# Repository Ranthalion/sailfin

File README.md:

View this project on [CADLAB.io](https://cadlab.io/project/23132). 

"# Sailfin"

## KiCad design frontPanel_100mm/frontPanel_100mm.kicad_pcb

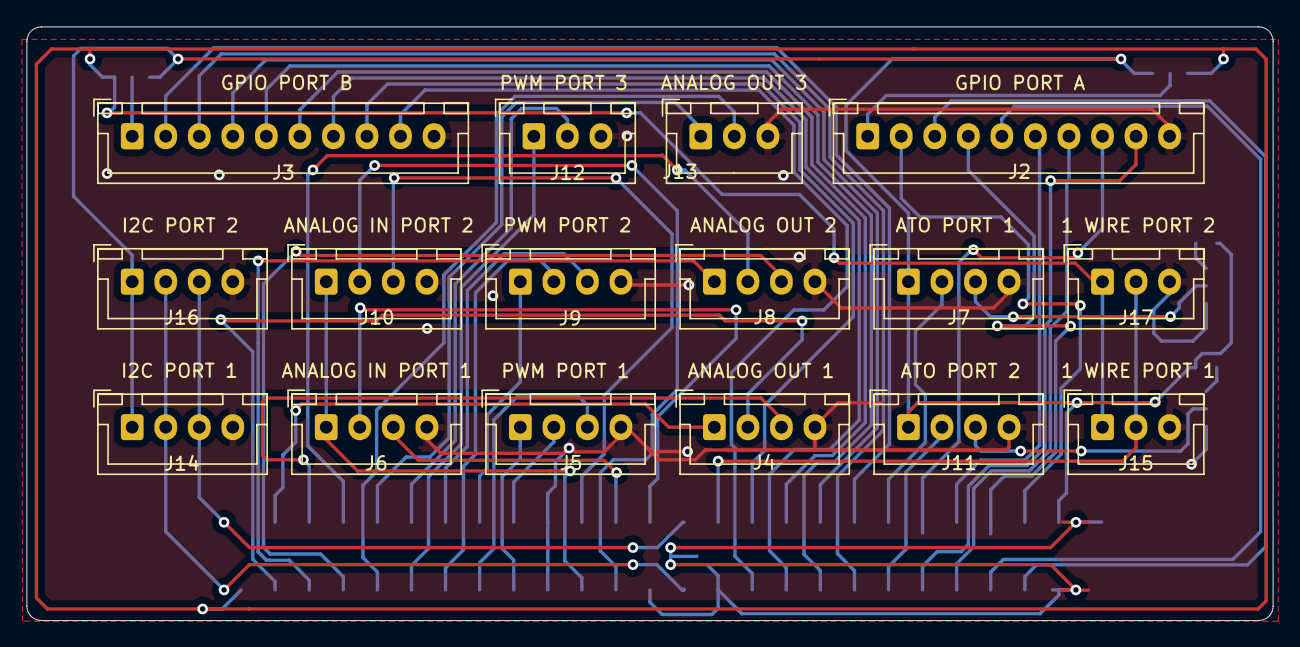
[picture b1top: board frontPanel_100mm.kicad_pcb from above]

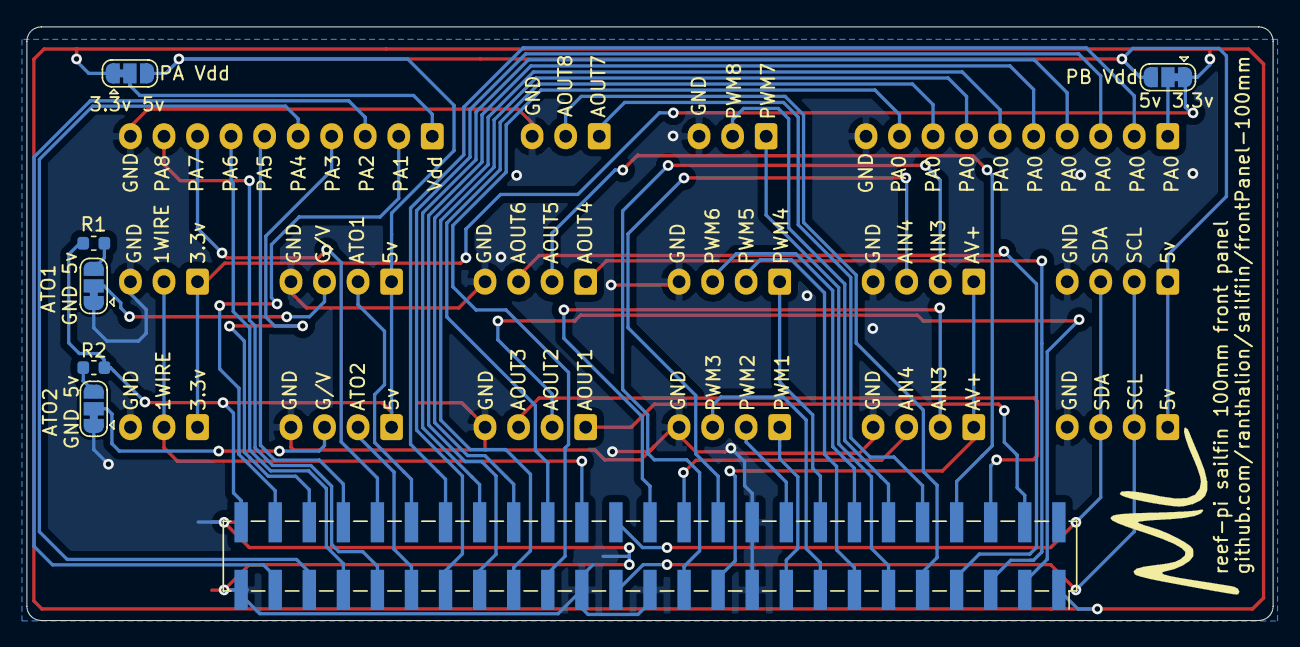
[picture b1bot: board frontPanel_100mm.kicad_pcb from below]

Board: 2 copper layers, 92.9 x 44.3 mm, 23 parts (7 on the bottom side), 51 nets.

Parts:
J1: Conn_02x25_Odd_Even; PinSocket_2x25_P2.54mm_Vertical_SMD
J2: GPIO PORT A; JST_XH_B10B-XH-A_1x10_P2.50mm_Vertical
J3: GPIO PORT B; JST_XH_B10B-XH-A_1x10_P2.50mm_Vertical
J4: ANALOG OUT 1; JST_XH_B04B-XH-A_1x04_P2.50mm_Vertical
J5: PWM PORT 1; JST_XH_B04B-XH-A_1x04_P2.50mm_Vertical
J6: ANALOG IN PORT 1; JST_XH_B04B-XH-A_1x04_P2.50mm_Vertical
J7: ATO PORT 1; JST_XH_B04B-XH-A_1x04_P2.50mm_Vertical
J8: ANALOG OUT 2; JST_XH_B04B-XH-A_1x04_P2.50mm_Vertical
J9: PWM PORT 2; JST_XH_B04B-XH-A_1x04_P2.50mm_Vertical
J10: ANALOG IN PORT 2; JST_XH_B04B-XH-A_1x04_P2.50mm_Vertical
J11: ATO PORT 2; JST_XH_B04B-XH-A_1x04_P2.50mm_Vertical
J12: PWM PORT 3; JST_XH_B03B-XH-A_1x03_P2.50mm_Vertical
J13: ANALOG OUT 3; JST_XH_B03B-XH-A_1x03_P2.50mm_Vertical
J14: I2C PORT 1; JST_XH_B04B-XH-A_1x04_P2.50mm_Vertical
J15: 1 WIRE PORT 1; JST_XH_B03B-XH-A_1x03_P2.50mm_Vertical
J16: I2C PORT 2; JST_XH_B04B-XH-A_1x04_P2.50mm_Vertical
J17: 1 WIRE PORT 2; JST_XH_B03B-XH-A_1x03_P2.50mm_Vertical
JP3: ATO1_Jumper; SolderJumper-3_P1.3mm_Bridged12_RoundedPad1.0x1.5mm
JP4: ATO2_Jumper; SolderJumper-3_P1.3mm_Bridged12_RoundedPad1.0x1.5mm
PA Vdd: PA Voltage; SolderJumper-3_P1.3mm_Bridged12_RoundedPad1.0x1.5mm
PB Vdd: PB Voltage; SolderJumper-3_P1.3mm_Bridged12_RoundedPad1.0x1.5mm
R1: 500; R_0603_1608Metric
R2: R_US; R_0603_1608Metric

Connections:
/1WIRE: J1.30, J15.2, J17.2
/3v3: J1.1, J15.1, J17.1, PA Vdd.1, PB Vdd.1
/5v: J1.50, J7.1, J11.1, J14.1, J16.1, PA Vdd.3, PB Vdd.3, R1.1, R2.1
/AIN1: J1.26, J6.2
/AIN2: J1.24, J6.3
/AIN3: J1.23, J10.2
/AIN4: J1.22, J10.3
/AOUT1: J1.4, J4.1
/AOUT2: J1.3, J4.2
/AOUT3: J1.6, J4.3
/AOUT4: J1.5, J8.1
/AOUT5: J1.8, J8.2
/AOUT6: J1.7, J8.3
/AOUT7: J1.10, J13.1
/AOUT8: J1.9, J13.2
/ATO1: J1.40, J7.2
/ATO2: J1.39, J11.2
/AV+: J1.21, J6.1, J10.1
/PA1: J1.48, J2.2
/PA2: J1.47, J2.3
/PA3: J1.46, J2.4
/PA4: J1.45, J2.5
/PA5: J1.44, J2.6
/PA6: J1.43, J2.7
/PA7: J1.42, J2.8
/PA8: J1.41, J2.9
/PB1: J1.38, J3.2
/PB2: J1.37, J3.3
/PB3: J1.36, J3.4
/PB4: J1.35, J3.5
/PB5: J1.34, J3.6
/PB6: J1.33, J3.7
/PB7: J1.32, J3.8
/PB8: J1.31, J3.9
/PWM1: J1.17, J5.1
/PWM2: J1.18, J5.2
/PWM3: J1.15, J5.3
/PWM4: J1.16, J9.1
/PWM5: J1.13, J9.2
/PWM6: J1.14, J9.3
/PWM7: J1.11, J12.1
/PWM8: J1.12, J12.2
/SCL: J1.27, J14.2, J16.2
/SDA: J1.28, J14.3, J16.3
GND: J1.19, J1.20, J1.25, J1.29, J1.49, J2.10, J3.10, J4.4, J5.4, J6.4, J7.4, J8.4, J9.4, J10.4, J11.4, J12.3, J13.3, J14.4, J15.3, J16.4, J17.3, JP3.1, JP4.1
unnamed: J2.1, PA Vdd.2
unnamed: J3.1, PB Vdd.2
unnamed: J7.3, JP3.2
unnamed: J11.3, JP4.2
unnamed: JP3.3, R1.2
unnamed: JP4.3, R2.2

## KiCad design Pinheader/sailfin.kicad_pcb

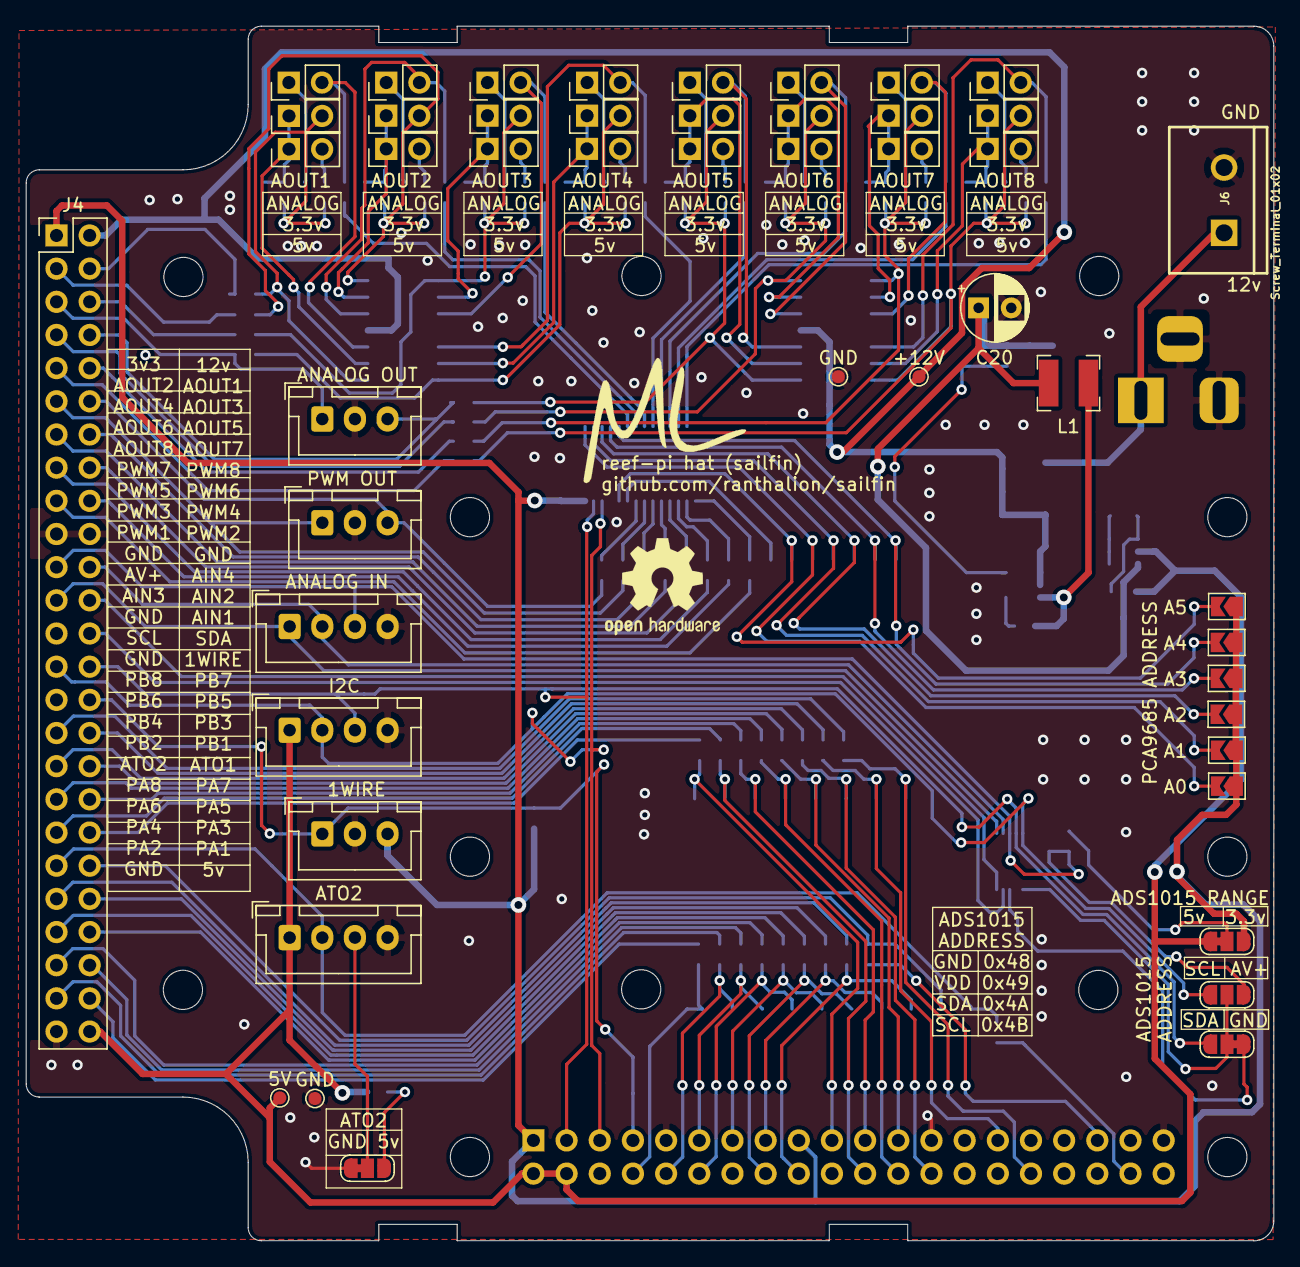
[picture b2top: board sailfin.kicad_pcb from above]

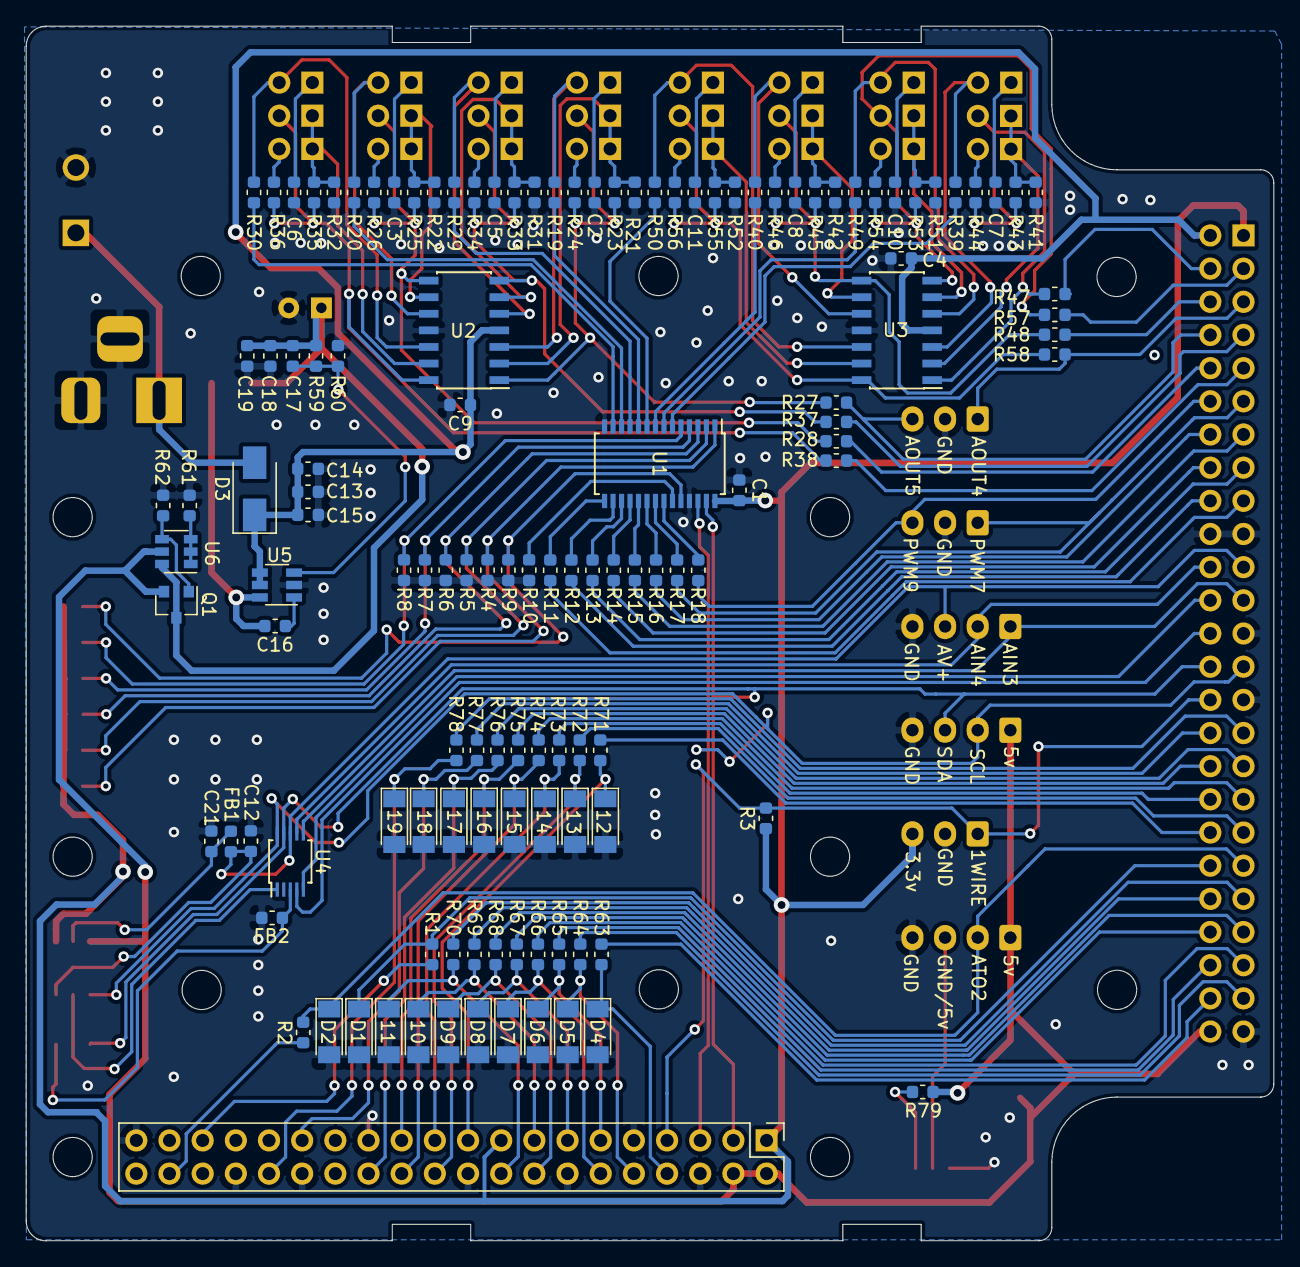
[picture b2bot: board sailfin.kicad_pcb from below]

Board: 2 copper layers, 95.5 x 93.0 mm, 177 parts (128 on the bottom side), 139 nets.

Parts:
5V: TestPoint_Pad_D1.0mm
10, 11, 12, 13, 14, 15, 16, 17, 18, 19: z3.3; D_MiniMELF
+12V: TestPoint_Pad_D1.0mm
C1, C4, C9: C; C_0603_1608Metric
C2, C3, C5, C6, C7, C8, C10, C11, C12, C15, C16, C21: 0.1uF; C_0603_1608Metric
C13, C14, C18, C19: 10uF; C_0603_1608Metric
C17: 22pF; C_0603_1608Metric
C20: 100uF; CP_Radial_D5.0mm_P2.50mm
D1, D2, D4, D5, D6, D7, D8, D9: z3.3; D_MiniMELF
D3: D_Schottky; D_SMA
FB1, FB2: NBQ160808T-182Y-N; R_0603_1608Metric
GND: TestPoint_Pad_D1.0mm
GND#2: TestPoint_Pad_D1.0mm
J1: AnalogIn; JST_XH_B04B-XH-A_1x04_P2.50mm_Vertical
J2: ATO1; JST_XH_B04B-XH-A_1x04_P2.50mm_Vertical
J3: Raspberry_Pi_2_3; PinHeader_2x20_P2.54mm_Vertical
J4: Conn_02x25_Odd_Even; PinHeader_2x25_P2.54mm_Vertical
J5: i2c; JST_XH_B04B-XH-A_1x04_P2.50mm_Vertical
J6: Screw_Terminal_01x02; SCREWTERMINAL-5MM-2
J7: 1wire; JST_XH_B03B-XH-A_1x03_P2.50mm_Vertical
J8: PwmOut; JST_XH_B03B-XH-A_1x03_P2.50mm_Vertical
J9: AnalogOut; JST_XH_B03B-XH-A_1x03_P2.50mm_Vertical
J19: Barrel_Jack_Switch; BarrelJack_Horizontal
JP1, JP2, JP3, JP4, JP5, JP6: ADDR; SolderJumper-2_P1.3mm_Open_TrianglePad1.0x1.5mm
JP7, JP8, JP13, JP14, JP19, JP20, JP25, JP26: JP_Analog; PinHeader_1x02_P2.54mm_Vertical
JP9, JP11, JP15, JP17, JP21, JP23, JP27, JP29: JP_3v3; PinHeader_1x02_P2.54mm_Vertical
JP10, JP12, JP16, JP18, JP22, JP24, JP28, JP30: JP_5v; PinHeader_1x02_P2.54mm_Vertical
JP31: SolderJumper_3_Open; SolderJumper-3_P1.3mm_Open_RoundedPad1.0x1.5mm
JP32, JP33: SolderJumper_3_Bridged12; SolderJumper-3_P1.3mm_Bridged12_RoundedPad1.0x1.5mm
JP34: Jumper_3_Bridged12; SolderJumper-3_P1.3mm_Bridged12_RoundedPad1.0x1.5mm
L1: 6.8uH; L_Bourns-SRN4018
Q1: MOSFET_PCH-DMG2307L; SOT-23
R1, R2, R11, R12, R13, R14, R15, R16, R17, R18, R27, R28, R37, R38, R47, R48, R57, R58, R63, R64, R65, R66, R67, R68, R69, R70, R71, R72, R73, R74, R75, R76, R77, R78: 220; R_0603_1608Metric
R3: 4.7k; R_0603_1608Metric
R4, R5, R6, R7, R8, R9, R10: 10k; R_0603_1608Metric
R19, R20, R29, R30, R39, R40, R49, R50: 20k; R_0603_1608Metric
R21, R22, R31, R32, R41, R42, R51, R52: 100k; R_0603_1608Metric
R23, R25, R33, R35, R43, R45, R53, R55: 220k; R_0603_1608Metric
R24, R26, R34, R36, R44, R46, R54, R56: 82k; R_0603_1608Metric
R59: 270k; R_0603_1608Metric
R60: 36k; R_0603_1608Metric
R61, R62: 22; R_0603_1608Metric
R79: 500; R_0603_1608Metric
U1: PCA9685PW; TSSOP-28_4.4x9.7mm_P0.65mm
U2, U3: LM324; SOIC-14_3.9x8.7mm_P1.27mm
U4: ADS1015IDGS; TSSOP-10_3x3mm_P0.5mm
U5: SY8113BADC; TSOT-23-6
U6: DMMT5401; SOT-23-6

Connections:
+3V3: C1.1, J3.1, J3.17, J4.1, J7.3, JP1.1, JP2.1, JP3.1, JP4.1, JP5.1, JP6.1, JP33.3, R3.1, U1.28
+5V: 5V.1, J2.1, J3.2, J3.4, J4.50, J5.1, JP33.1, Q1.2, R79.2, U6.5
+12V: +12V.1, C4.1, C9.1, C13.1, C14.1, C15.1, D3.1, J4.2, U2.4, U3.4, U5.4, U5.5
/1WIRE: J3.7, J4.30, J7.1, R3.2
/AIN1: J4.26, U4.4
/AIN2: J4.24, U4.5
/AIN3: J1.1, J4.23, U4.6
/AIN4: J1.2, J4.22, U4.7
/AOUT1: J4.4, R47.1
/AOUT2: J4.3, R57.1
/AOUT3: J4.6, R48.1
/AOUT4: J4.5, J9.1, R58.1
/AOUT5: J4.8, J9.3, R27.1
/AOUT6: J4.7, R37.1
/AOUT7: J4.10, R28.1
/AOUT8: J4.9, R38.1
/ATO1: D1.1, J4.40, R1.2
/ATO2: D2.1, J2.2, J4.39, R2.2
/AV+: C12.1, FB1.1, J1.3, J4.21, JP31.1, U4.8
/GPIO5: 18.1, J3.29, R77.1
/GPIO7: 17.1, J3.26, R76.1
/GPIO8: 15.1, J3.24, R74.1
/GPIO9: 14.1, J3.21, R73.1
/GPIO10: 12.1, J3.19, R71.1
/GPIO11: 16.1, J3.23, R75.1
/GPIO12: 19.1, J3.32, R78.1
/GPIO14: D4.1, J3.8, R63.1
/GPIO15: D5.1, J3.10, R64.1
/GPIO17: D6.1, J3.11, R65.1
/GPIO18: D7.1, J3.12, R66.1
/GPIO19: J3.35, R1.1
/GPIO20: J3.38, R2.1
/GPIO22: 10.1, J3.15, R69.1
/GPIO23: D9.1, J3.16, R68.1
/GPIO24: 11.1, J3.18, R70.1
/GPIO25: 13.1, J3.22, R72.1
/GPIO27: D8.1, J3.13, R67.1
/PA1: J4.48, R63.2
/PA2: J4.47, R64.2
/PA3: J4.46, R65.2
/PA4: J4.45, R66.2
/PA5: J4.44, R67.2
/PA6: J4.43, R68.2
/PA7: J4.42, R69.2
/PA8: J4.41, R70.2
/PB1: J4.38, R71.2
/PB2: J4.37, R72.2
/PB3: J4.36, R73.2
/PB4: J4.35, R74.2
/PB5: J4.34, R75.2
/PB6: J4.33, R76.2
/PB7: J4.32, R77.2
/PB8: J4.31, R78.2
/PWM1: J4.17, R11.1
/PWM2: J4.18, R12.1
/PWM3: J4.15, R13.1
/PWM4: J4.16, R14.1
/PWM5: J4.13, R15.1
/PWM6: J4.14, R16.1
/PWM7: J4.11, J8.1, R17.1
/PWM8: J4.12, J8.3, R18.1
/PWM/A0: JP1.2, R4.1, U1.1
/PWM/A1: JP2.2, R5.1, U1.2
/PWM/A2: JP3.2, R6.1, U1.3
/PWM/A3: JP4.2, R7.1, U1.4
/PWM/A4: JP5.2, R8.1, U1.5
/PWM/A5: JP6.2, R9.1, U1.24
/PWM/LED0: R39.2, U1.6
/PWM/LED1: R49.2, U1.7
/PWM/LED2: R40.2, U1.8
/PWM/LED3: R50.2, U1.9
/PWM/LED4: R19.2, U1.10
/PWM/LED5: R29.2, U1.11
/PWM/LED6: R20.2, U1.12
/PWM/LED7: R30.2, U1.13
/SCL: J3.5, J4.27, J5.2, JP31.3, U1.26, U4.10
/SDA: J3.3, J4.28, J5.3, JP32.3, U1.27, U4.9
GND: 10.2, 11.2, 12.2, 13.2, 14.2, 15.2, 16.2, 17.2, 18.2, 19.2, C1.2, C2.2, C3.2, C4.2, C5.2, C6.2, C7.2, C8.2, C9.2, C10.2, C11.2, C12.2, C13.2, C14.2, C15.2, C18.2, C19.2, C20.2, C21.2, D1.2, D2.2, D4.2, D5.2, D6.2, D7.2, D8.2, D9.2, FB2.1, GND.1, GND#2.1, J1.4, J2.4, J3.6, J3.9, J3.14, J3.20, J3.25, J3.30, J3.34, J3.39, J4.19, J4.20, J4.25, J4.29, J4.49, J5.4, J6.2, J7.2, J8.2, J9.2, J19.2, J19.3, JP34.1, R4.2, R5.2, R6.2, R7.2, R8.2, R9.2, R10.1, R21.1, R22.1, R31.1, R32.1, R41.1, R42.1, R51.1, R52.1, R60.2, R61.2, R62.2, U1.14, U1.25, U2.11, U3.11, U5.2
unnamed: C2.1, JP7.1
unnamed: C3.1, JP8.1
unnamed: C5.1, JP13.1
unnamed: C6.1, JP14.1
unnamed: C7.1, JP19.1
unnamed: C8.1, JP20.1
unnamed: C10.1, JP25.1
unnamed: C11.1, JP26.1
unnamed: C16.1, L1.1, U5.6
unnamed: C16.2, U5.1
unnamed: C17.1, C18.1, C19.1, C20.1, L1.2, Q1.3, R59.1, U6.6
unnamed: C17.2, R59.2, R60.1, U5.3
unnamed: C21.1, FB1.2, JP33.2
unnamed: D3.2, J6.1, J19.1
unnamed: FB2.2, JP32.1, U4.3
unnamed: J2.3, JP34.2
unnamed: JP7.2, R19.1, U2.3
unnamed: JP8.2, R20.1, U2.10
unnamed: JP9.2, R23.2, R24.2, R27.2, U2.1
unnamed: JP9.1, JP10.1, R21.2, R23.1, U2.2
unnamed: JP10.2, R24.1
unnamed: JP11.1, JP12.1, R22.2, R25.1, U2.9
unnamed: JP11.2, R25.2, R26.2, R28.2, U2.8
unnamed: JP12.2, R26.1
unnamed: JP13.2, R29.1, U2.5
unnamed: JP14.2, R30.1, U2.12
unnamed: JP15.1, JP16.1, R31.2, R33.1, U2.6
unnamed: JP15.2, R33.2, R34.2, R37.2, U2.7
unnamed: JP16.2, R34.1
unnamed: JP17.1, JP18.1, R32.2, R35.1, U2.13
unnamed: JP17.2, R35.2, R36.2, R38.2, U2.14
unnamed: JP18.2, R36.1
unnamed: JP19.2, R39.1, U3.3
unnamed: JP20.2, R40.1, U3.10
unnamed: JP21.1, JP22.1, R41.2, R43.1, U3.2
unnamed: JP21.2, R43.2, R44.2, R47.2, U3.1
unnamed: JP22.2, R44.1
unnamed: JP23.1, JP24.1, R42.2, R45.1, U3.9
unnamed: JP23.2, R45.2, R46.2, R48.2, U3.8
unnamed: JP24.2, R46.1
unnamed: JP25.2, R49.1, U3.5
unnamed: JP26.2, R50.1, U3.12
unnamed: JP27.1, JP28.1, R51.2, R53.1, U3.6
unnamed: JP27.2, R53.2, R54.2, R57.2, U3.7
unnamed: JP28.2, R54.1
unnamed: JP29.1, JP30.1, R52.2, R55.1, U3.13
unnamed: JP29.2, R55.2, R56.2, R58.2, U3.14
unnamed: JP30.2, R56.1
unnamed: JP31.2, JP32.2, U4.1
unnamed: JP34.3, R79.1
unnamed: Q1.1, R62.1, U6.4
unnamed: R10.2, U1.23
unnamed: R11.2, U1.15
unnamed: R12.2, U1.16
unnamed: R13.2, U1.17
unnamed: R14.2, U1.18
unnamed: R15.2, U1.19
unnamed: R16.2, U1.20
unnamed: R17.2, U1.21
unnamed: R18.2, U1.22
unnamed: R61.1, U6.1, U6.2, U6.3

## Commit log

2020-04-08 sailfin schematic
2020-04-08 init
2020-04-11 100mm front panel
2020-04-19 card edge revision
2020-04-19 Tweak front panel size
2020-07-21 Backlink to CADLAB.io has been added.
